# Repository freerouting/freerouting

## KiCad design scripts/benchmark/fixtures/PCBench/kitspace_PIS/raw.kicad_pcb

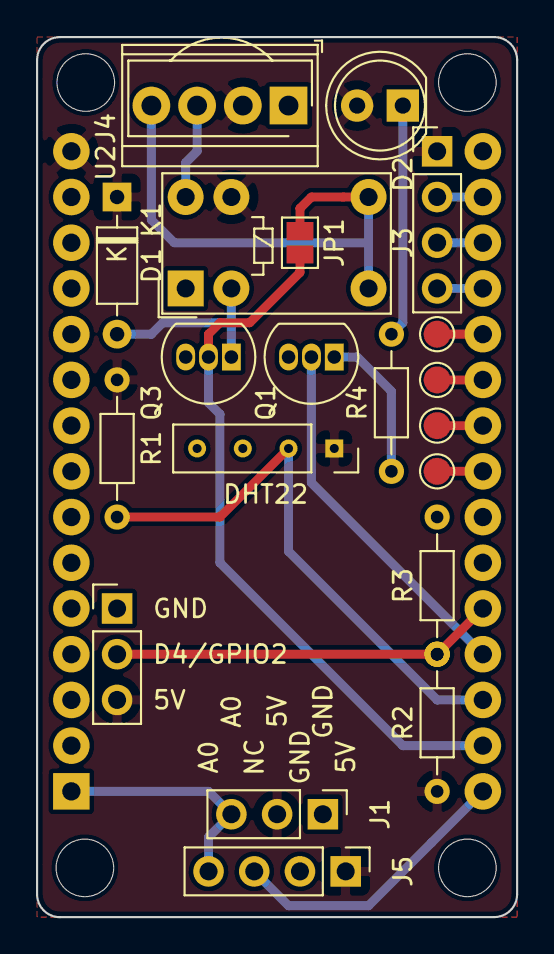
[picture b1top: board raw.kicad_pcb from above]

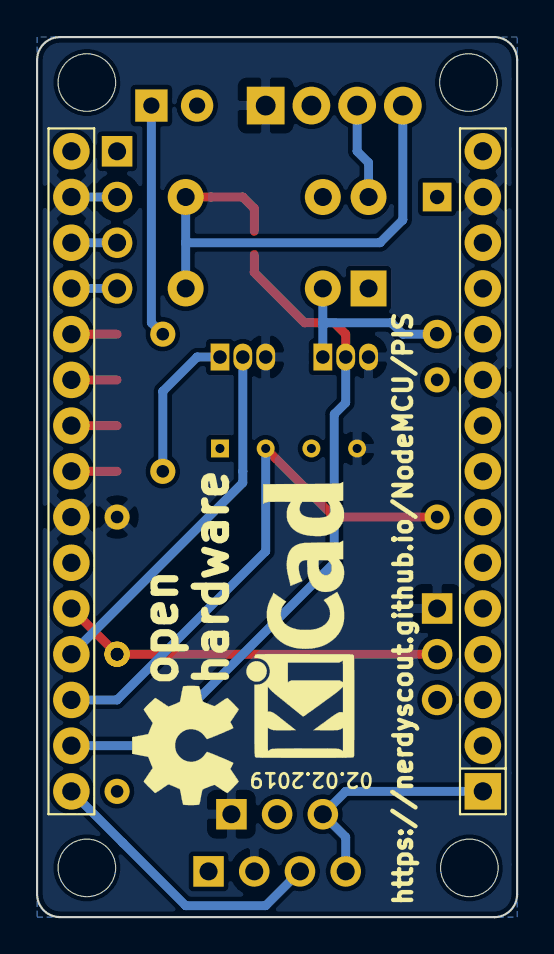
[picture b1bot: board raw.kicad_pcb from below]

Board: 2 copper layers, 26.7 x 48.9 mm, 24 parts (3 on the bottom side), 19 nets.

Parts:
D1: 1N4148; D_DO-35_SOD27_P7.62mm_Horizontal
D2: LED; LED_D5.0mm
J1: Capacitive Sensor; PinHeader_1x03_P2.54mm_Vertical
J2: Conn_01x03; PinHeader_1x03_P2.54mm_Vertical
J3: Serial; PinHeader_1x04_P2.54mm_Vertical
J4: Screw_Terminal_01x04; TerminalBlock_TE_282834-4_1x04_P2.54mm_Horizontal
J5: Resistive Sensor; PinHeader_1x04_P2.54mm_Vertical
JP1: NO; SolderJumper-2_P1.3mm_Open_Pad1.0x1.5mm
K1: G5V-1; Relay_SPDT_Omron_G5V-1
LOGO1: Logo_Open_Hardware_Small; OSHW-Symbol_6.7x6mm_SilkScreen
LOGO2: Logo_Open_Hardware_Small; KiCad-Logo_6mm_SilkScreen
Q1, Q3: BC547; TO-92_Inline
R1, R2, R3: 10k; R_Axial_DIN0204_L3.6mm_D1.6mm_P7.62mm_Horizontal
R4: 100; R_Axial_DIN0204_L3.6mm_D1.6mm_P7.62mm_Horizontal
TP1: CLK; TestPoint_Pad_D1.5mm
TP2: MISO; TestPoint_Pad_D1.5mm
TP3: MOSI; TestPoint_Pad_D1.5mm
TP4: CS; TestPoint_Pad_D1.5mm
U1: NodeMCU1.0(ESP-12E); NodeMCU_Amica
U2: TSOP17xx; Vishay_CAST-3Pin
U4: DHT11; PinSocket_1x04_P2.54mm_Vertical

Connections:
+5V: D1.1, D2.2, J1.2, J2.3, J3.1, J4.2, J5.1, K1.9, R1.2, R2.2, U1.15, U2.2, U4.1
A0: J1.3, J5.4, U1.1
Contact: J2.2, R2.1, R3.2, U1.26
DHT: R1.1, U1.28, U4.2
Dig: J5.3, U1.30
GND: J1.1, J2.1, J3.2, J4.1, J5.2, Q1.3, Q3.3, R3.1, U1.10, U1.14, U1.17, U1.24, U2.1, U4.4
LED: Q1.2, U1.27
unnamed: D1.2, K1.2, Q3.1
unnamed: D2.1, R4.2
unnamed: J4.3, K1.10
unnamed: J4.4, JP1.2, K1.5, K1.6, U2.3
unnamed: Q1.1, R4.1
unnamed: TP1.1, U1.23
unnamed: TP2.1, U1.22
unnamed: TP3.1, U1.21
unnamed: TP4.1, U1.20
Relay: JP1.1, Q3.2, U1.29
RxD: J3.4, U1.19
TxD: J3.3, U1.18

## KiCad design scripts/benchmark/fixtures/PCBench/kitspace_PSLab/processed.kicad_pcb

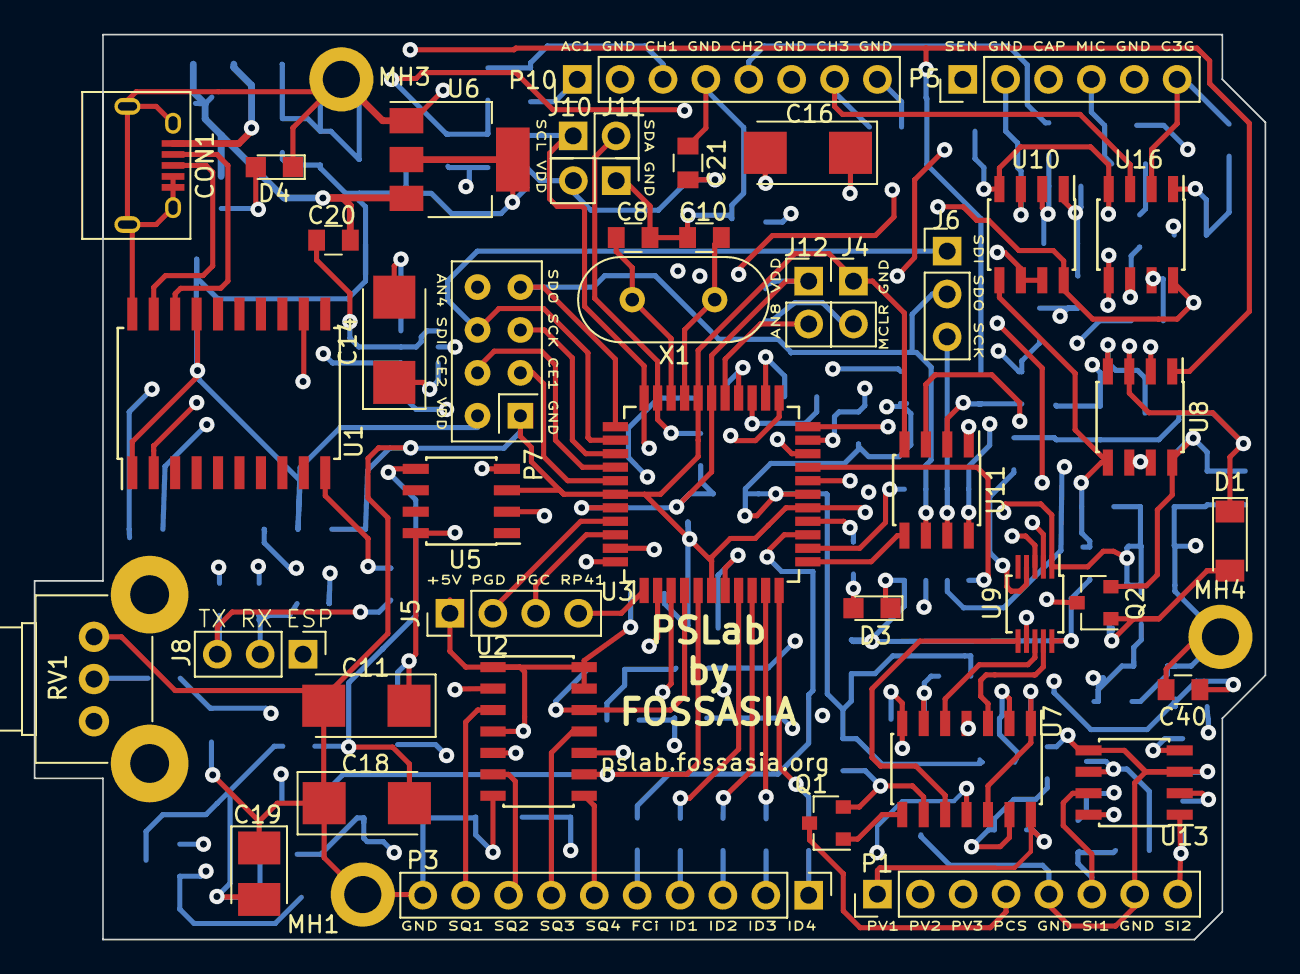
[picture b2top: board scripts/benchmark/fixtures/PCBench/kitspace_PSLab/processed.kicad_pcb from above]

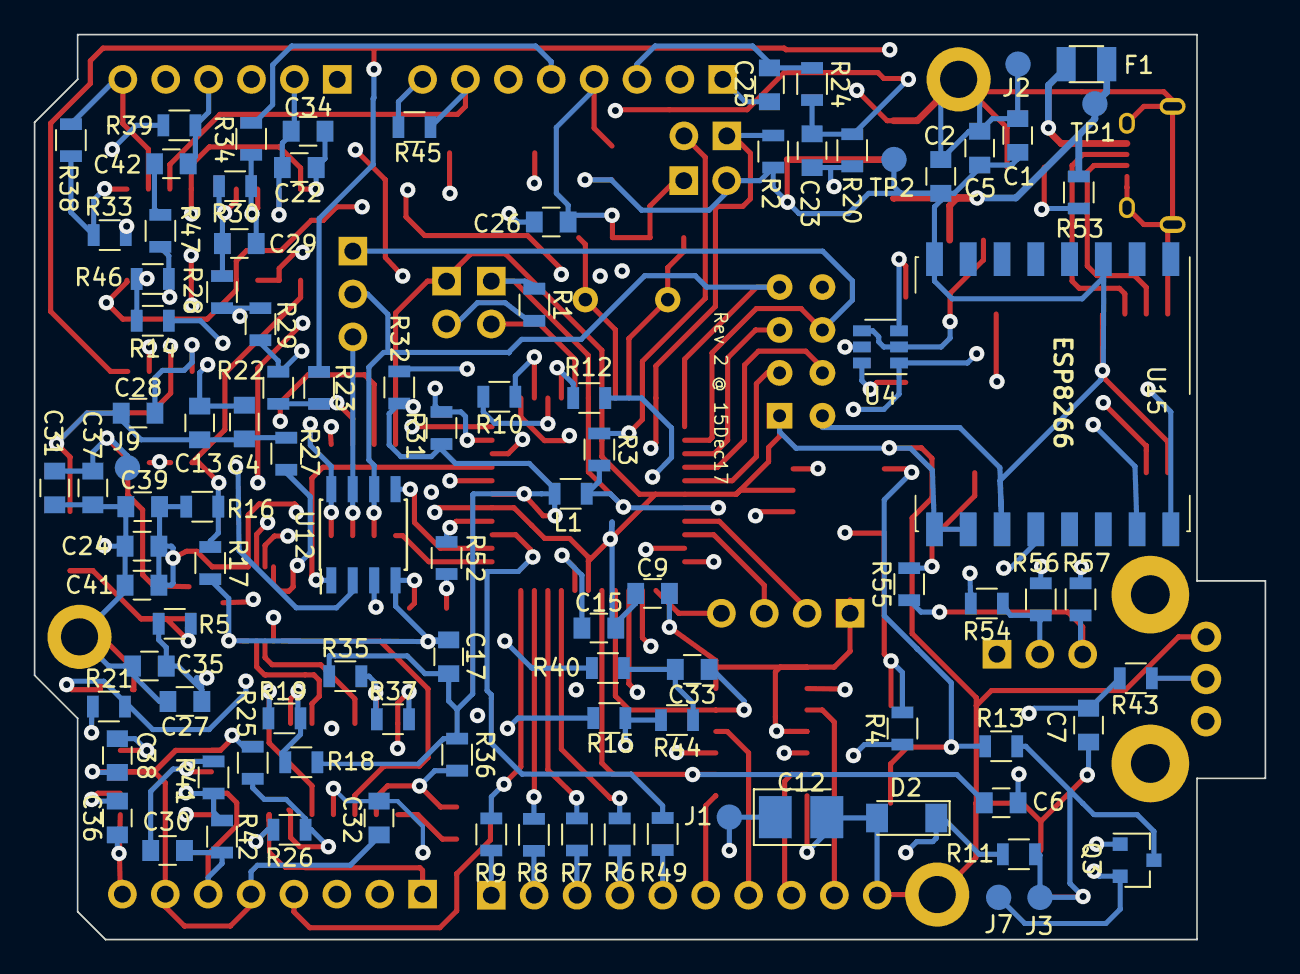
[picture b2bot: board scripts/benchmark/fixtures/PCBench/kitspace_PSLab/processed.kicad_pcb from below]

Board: 4 copper layers, 72.9 x 53.6 mm, 144 parts (99 on the bottom side), 114 nets.

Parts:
C1, C2, C4, C5, C9, C13, C17, C22, C24, C25, C26, C27, C28, C31, C32, C34, C35, C37, C38, C39, C41: 0.1u; C_0805
C6, C15, C21, C33: 10u; C_0805
C7, C40: 10nF; C_0805
C8, C10: 15pF; C_0805
C11, C14, C16, C18: 100u; CP_Tantalum_Case-C_EIA-6032-28_Reflow
C12, C19: 33u; CP_Tantalum_Case-B_EIA-3528-21_Reflow
C20, C42: 1u; C_0805
C23, C29: 3p3; C_0805
C30, C36: 1nF; C_0805
CON1: USB-MICRO-B; USB_Micro-B
D1, D2: 6V8; D_MiniMELF
D3, D4: LED; LED_0805
F1: 0.5A; Fuse_SMD1206_Reflow
J1: V+; Measurement_Point_Round-SMD-Pad_Small
J2: GND; Measurement_Point_Round-SMD-Pad_Small
J3: V-; Measurement_Point_Round-SMD-Pad_Small
J4: Ex-I; Pin_Header_Straight_1x02_Pitch2.54mm
J5: PG_Pins; Pin_Header_Straight_1x04_Pitch2.54mm
J6: Exp; Pin_Header_Straight_1x03_Pitch2.54mm
J7: VR-; Measurement_Point_Round-SMD-Pad_Small
J8: TX_RX_ES; Pin_Header_Straight_1x03_Pitch2.54mm
J9: VR+; Measurement_Point_Round-SMD-Pad_Small
J10: I2C-I; Pin_Header_Straight_1x02_Pitch2.54mm
J11: I2C-II; Pin_Header_Straight_1x02_Pitch2.54mm
J12: Ex-II; Pin_Header_Straight_1x02_Pitch2.54mm
L1: 10uH; L_0805
MH1, MH3, MH4: M; MountingHole_2.2mm_M2_ISO14580_Pad
P1: CONN_01X08; Pin_Header_Straight_1x08_Pitch2.54mm
P3: DIO; Pin_Header_Straight_1x10_Pitch2.54mm
P5: sen-cap; Pin_Header_Straight_1x06_Pitch2.54mm
P7: NRF; nRF24L01_Breakout_2
P10: Analog; Pin_Header_Straight_1x08_Pitch2.54mm
Q1, Q3: MMBT3906; SOT-23
Q2: MMBT3904; SOT-23
R1, R2, R3, R10, R14, R16, R17, R18, R19, R21, R22, R23, R25, R28, R29, R31, R32, R33, R35, R37, R38, R39, R42: 10K; R_0805
R4, R13, R54, R55, R56, R57: 18; R_0805
R5, R11, R27, R36, R47: 1K; R_0805
R6, R7, R8, R9: 200; R_0805
R12, R15, R26, R41, R43, R44, R52, R53: 5K1; R_0805
R20, R30, R40, R46: 200K; R_0805
R24, R34, R45: 1M; R_0805
R49: 560; R_0805
RV1: 47K; Potentiometer_Alps_RK09K_Vertical
TP1: 5V; Measurement_Point_Round-SMD-Pad_Small
TP2: Vdd; Measurement_Point_Round-SMD-Pad_Small
U1: MCP2200; SOIC-20W_7.5x12.8mm_Pitch1.27mm
U2: 74HC126; SOIC-14_3.9x8.7mm_Pitch1.27mm
U3: PIC24EP256GP204; TQFP-44_10x10mm_Pitch0.8mm
U4: TC1240A; SOT-23-6
U5: 7660; SOIC-8_3.9x4.9mm_Pitch1.27mm
U6: LM1117-3.3; SOT-223
U7: LM324; SOIC-14_3.9x8.7mm_Pitch1.27mm
U8, U10, U13, U16: TL082; SOIC-8_3.9x4.9mm_Pitch1.27mm
U9: MCP4728; MSOP-10_3x3mm_Pitch0.5mm
U11, U12: 6S21; SOIC-8_3.9x4.9mm_Pitch1.27mm
U15: ESP8266; Hopref_RFM9XW_SMD
X1: 12MHz; Crystal_HC49-U_Vertical

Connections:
12MHz: C8.2, U1.2, U3.31, X1.1
+5V: C9.2, C20.2, F1.2, J5.1, R53.2, TP1.1, U2.1, U2.4, U2.10, U2.13, U2.14, U4.1, U6.3
/CAP: P5.3, R10.1, U3.24
/D+: CON1.3, U1.19
/D-: CON1.2, U1.18
/ERxD: R56.1, U15.15
/ESPROG: J8.1, U15.12
/ETxD: R57.1, U15.16
/FCin: P3.5, R49.2
/I/O Processing/DAC1: U7.3, U9.9
/I/O Processing/DAC2: U7.5, U9.8
/I/O Processing/DAC4: U7.10, U9.6
/ID1: R6.2, U3.8
/ID2: R7.2, U3.9
/ID3: R8.2, U3.10
/ID4: R9.2, U3.11
/MCLR: J4.2, R1.2, U3.18
/MRxD: R54.2, U1.12
/MTxD: R55.2, U1.10
/RxD: J8.2, R54.1, R56.2, U3.43
/SEN: P5.1, R12.1, U3.26
/SQR1: P3.9, U2.3
/SQR2: P3.8, U2.6
/SQR3: P3.7, U2.11
/SQR4: P3.6, U2.8
/TxD: J8.3, R55.1, R57.2, U3.44
ACH1: C25.2, P10.1
AN4: P7.8, U3.23
AN8: J12.2, U3.27
AVdd: C17.2, C24.2, C39.2, C41.2, L1.1, R12.2, R16.2, R18.1, R22.2, R29.1, R31.2, R32.2, R35.1, R36.1, R39.2, U3.17, U9.1, U11.8, U12.8
CH1: C25.1, P10.3, R24.1
CH1out: U3.22, U11.1
CH2: P10.5, R34.1
CH2out: U3.19, U12.1
CH3: P10.7, R45.2, U16.3
CH3.GAIN: P5.6, R38.1, U16.2
CH3out: R32.1, R33.1, U3.20
CS.CH1: U3.12, U11.5
CS.CH2: U3.13, U12.5
CS.E1: P7.3, U3.38
CS.E2: P7.4, U3.37
GND: C1.2, C2.1, C4.2, C5.2, C7.2, C8.1, C9.1, C10.1, C11.2, C12.2, C13.1, C15.2, C17.1, C18.1, C19.1, C20.1, C21.2, C22.1, C24.1, C26.1, C27.2, C28.1, C31.1, C32.2, C34.1, C35.1, C37.1, C38.1, C39.1, C40.2, C41.1, CON1.4, CON1.5, CON1.6, D1.1, D2.2, D3.1, D4.1, J2.1, J4.1, J11.1, MH1.1, MH3.1, MH4.1, P1.5, P1.7, P3.10, P5.2, P5.5, P7.1, P10.2, P10.4, P10.6, P10.8, R17.2, R25.1, R27.2, R40.2, R45.1, RV1.1, U1.20, U2.7, U3.6, U3.16, U3.29, U3.39, U4.2, U4.4, U5.3, U6.1, U8.3, U9.10, U10.3, U11.4, U12.4, U13.3, U13.5, U15.9, U15.10, U16.5
MIC: C42.2, P5.4, R39.1
MICout: R14.1, R31.1, U3.21
unnamed: C6.2, RV1.3
unnamed: C7.1, R41.2, R42.1, R43.2
unnamed: C10.2, U3.30, X1.2
unnamed: C11.1, R4.2, U4.5, U5.8
unnamed: C14.1, U4.6
unnamed: C14.2, U4.3
unnamed: C15.1, U3.7
unnamed: C16.1, U5.2
unnamed: C16.2, U5.4
unnamed: C18.2, R13.2, U5.5
unnamed: C23.1, R20.1, R23.2, U8.1
unnamed: C23.2, R20.2, R24.2, U8.2
unnamed: C29.1, R28.1, R30.1, U10.1
unnamed: C29.2, R30.2, R34.2, U10.2
unnamed: C30.2, R41.1, U13.6
unnamed: C33.2, R40.1, R44.1
unnamed: C36.2, R15.1, U13.2
unnamed: C40.1, R15.2, R21.2, R44.2
unnamed: C42.1, R47.2
unnamed: CON1.1, F1.1
unnamed: D1.2, Q2.1, R5.2
unnamed: D2.1, Q3.1, R11.1
unnamed: D3.2, R52.1
unnamed: D4.2, R53.1
unnamed: P3.1, R9.1
unnamed: P3.2, R8.1
unnamed: P3.3, R7.1
unnamed: P3.4, R6.1
unnamed: Q1.1, U7.8
unnamed: Q1.2, R36.2, U7.9
unnamed: R10.2, U3.25
unnamed: R14.2, R46.2, U16.7
unnamed: R16.1, R17.1, U8.5, U10.5
unnamed: R18.2, R19.1, U7.2
unnamed: R19.2, U7.1, U7.12
unnamed: R22.1, R23.1, U11.2
unnamed: R25.2, R26.1, U7.13
unnamed: R27.1, U9.4
unnamed: R28.2, R29.2, U12.2
unnamed: R33.2, R38.2, U16.1
unnamed: R35.2, R37.1, U7.6
unnamed: R43.1, RV1.2
unnamed: R46.1, R47.1, U16.6
unnamed: R49.1, U3.14
unnamed: U2.2, U3.2
unnamed: U2.5, U3.3
unnamed: U10.6, U10.7, U12.3
unnamed: U8.6, U8.7, U11.3
PCS: P1.4, Q1.3
PGC2: J5.3, U3.42
PGD2: J5.2, U3.41
PVS1: P1.1, R26.2, U7.14
PVS2: P1.2, R37.2, U7.7
PVS3: P1.3, U9.7
RP41: J5.4, U3.1
RP147: R52.2, U3.15
SCK: J6.3, P7.5, U3.36, U11.7, U12.7
SCL: J10.1, R2.1, U3.33, U9.2
SDA: J10.2, R3.1, U3.32, U9.3
SDI: J6.1, P7.6, U3.35
SDO: J6.2, P7.7, U3.34, U11.6, U12.6
SINE1: C30.1, P1.6, R42.2, U13.7
SINE2: C36.1, P1.8, R21.1, U13.1
SQ3: C33.1, U2.12, U3.4
SQ4: C6.1, U2.9, U3.5
V+: C12.1, C27.1, C35.2, J1.1, Q2.3, R4.1, R5.1, U7.4, U13.8
V-: C19.2, C32.1, C38.2, J3.1, Q3.3, R11.2, R13.1, U7.11, U13.4
VR+: C26.2, C31.2, C37.2, J9.1, Q2.2, U8.8, U10.8, U16.8
VR-: C22.2, C28.2, C34.2, J7.1, Q3.2, U8.4, U10.4, U16.4
Vdd: C1.1, C2.2, C4.1, C5.1, C13.2, C21.1, J11.2, J12.1, L1.2, P7.2, R1.1, R2.2, R3.2, TP2.1, U1.1, U1.17, U3.28, U3.40, U6.2, U6.4, U15.3, U15.8, U15.11

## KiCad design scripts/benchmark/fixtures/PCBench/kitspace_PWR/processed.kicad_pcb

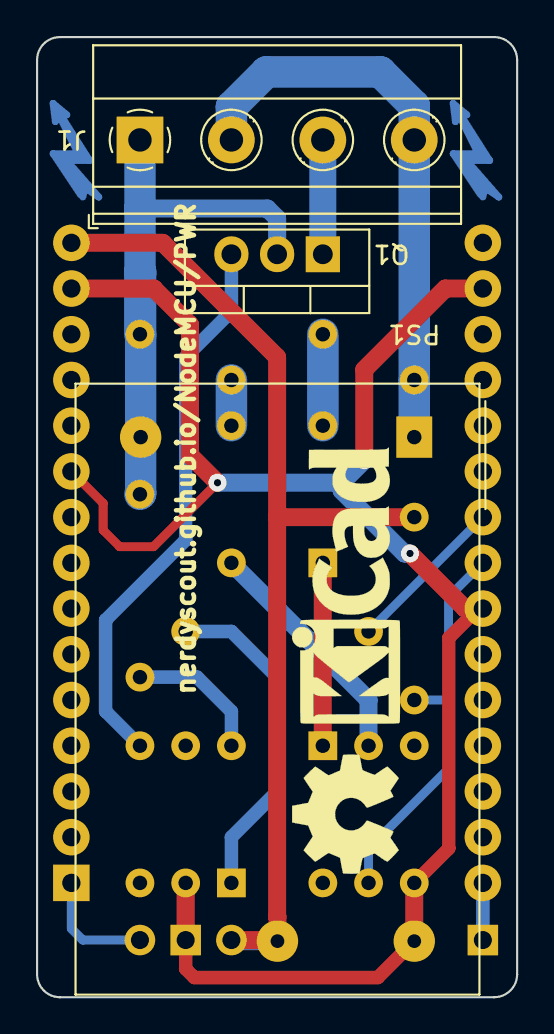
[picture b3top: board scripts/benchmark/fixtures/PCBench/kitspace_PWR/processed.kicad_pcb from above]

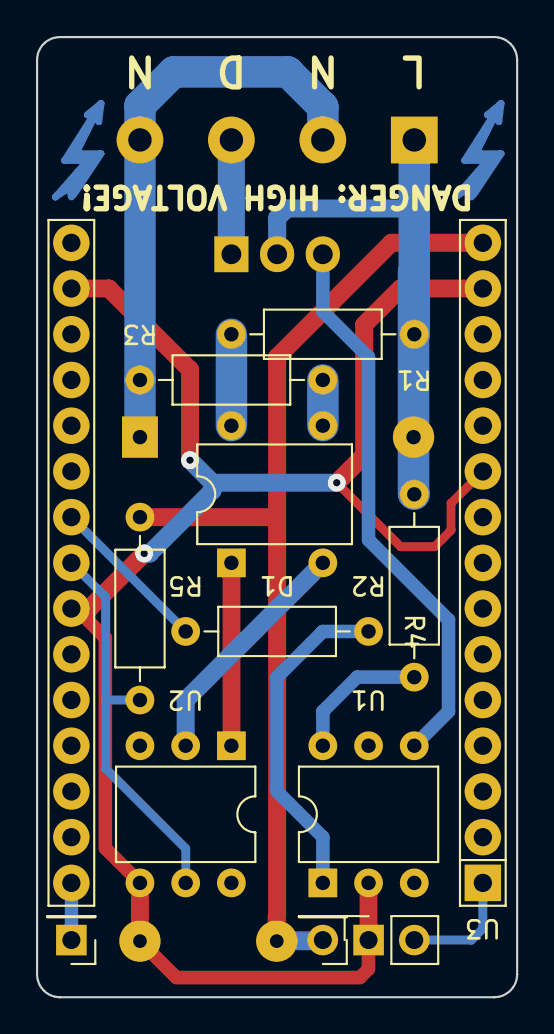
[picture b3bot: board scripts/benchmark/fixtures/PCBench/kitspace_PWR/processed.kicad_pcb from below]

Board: 2 copper layers, 26.7 x 53.3 mm, 19 parts (14 on the bottom side), 16 nets.

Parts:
D1: DF06M; Diode_Bridge_DIP-4_W7.62mm_P5.08mm
J1: Screw_Terminal_01x04; TerminalBlock_Phoenix_MKDS-1,5-4-5.08_1x04_P5.08mm_Horizont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
J2, J5: Conn_01x01; PinHeader_1x01_P2.54mm_Vertical
J3: Conn_01x02; PinSocket_1x02_P2.54mm_Vertical
LOGO1: Logo_Open_Hardware_Small; OSHW-Symbol_6.7x6mm_SilkScreen
LOGO2: Logo_Open_Hardware_Small; KiCad-Logo_6mm_SilkScreen
PS1: IRM-02-5; Converter_ACDC_MeanWell_IRM-02-xx_THT
Q1: TIC206; TO-220-3_Vertical
R1, R2, R3, R4, R5: R; R_Axial_DIN0207_L6.3mm_D2.5mm_P10.16mm_Horizontal
SYM1, SYM2: SYM_Flash_Small; Symbol_Highvoltage_Type1_CopperTop_Small
U1: MOC3021M; DIP-6_W7.62mm
U2: 4N25; DIP-6_W7.62mm
U3: NodeMCU1.0(ESP-12E); NodeMCU_Amica_WithMountingHoles

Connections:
+5V: J5.1, PS1.4, R5.2, U3.15
GND: J3.1, PS1.3, U1.2, U2.4, U3.10, U3.14, U3.17, U3.24
NEUT: J1.2, J1.4, PS1.1, R3.1
unnamed: D1.1, U2.1
unnamed: D1.2, U2.2
unnamed: D1.3, R3.2
unnamed: D1.4, R1.2
unnamed: J1.3, Q1.1
unnamed: J2.1, U3.30
unnamed: J3.2, U3.1
unnamed: Q1.3, U1.4
unnamed: R2.2, U1.6
unnamed: R4.1, U1.1
VAC: J1.1, PS1.2, Q1.2, R1.1, R2.1
dim: R4.2, U3.22
zero: R5.1, U2.5, U3.23
